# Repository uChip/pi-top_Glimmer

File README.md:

pi-top_Glimmer  
==============

NOTE: This project is a work in progress and is subject to change.  See the Status section for recent changes.  

This repository contains the design files and write-up for pi-top_Glimmer.  

Note: I have no affiliation with pi-top other than being a customer.  

The pi-top Glimmer is an accessory board for the [pi-topCEED](https://pi-top.com/product/ceed).  It also fits the pi-top laptop.  The board reconstitutes the Raspberry Pi GPIO connector. Unlike the [pi-topPROTO](https://pi-top.com/buy/addon) the Glimmer places the connector optimally for connecting the ["T-Cobbler Plus - GPIO Breakout"](https://www.adafruit.com/product/2028) or the ["Pi Wedge"](https://www.sparkfun.com/products/13717).  

<picture>

The board includes support for an IR Receiver (TSOP38238 or similar) for IR remote control of the pi-top.  An on board ATmega328p (programmable Arduino style) monitors the Raw, 5V and 3.3V voltage levels of the pi-top power supply to help detect if the supply is overloaded.  

The pi-top Glimmer passes the accessory buss through to the other end of the board so that the pi-topSPEAKER or other accessories can be plugged in.  An effort has been made to use a minimum of Raspberry Pi GPIO resources so that as many HATs as possible will still work.  The pi-top HUB board commits GPIO's 7, 9,10 & 11 as the SPI buss with HUB board select on GPIO 7 (CE1_N).  To this the pi-top Glimmer adds the use of GPIOs 2 & 3 as the I2C buss (sharable with other boards) and resides at I2C address 110.  The IR Receiver is optionally connected via solder jumper to GPIO 24 (pin 18).  

Finally, the board includes an 8x8 LED (single color, on/off) array that is refreshed from the Arduino and commanded from the pi-top's Raspberry Pi.  

The software folder contains a "sketch" that is source code for the Arduino which can be changed and updated from the pi-top.  

The board is built using a combination of through-hole and (larger scale) surface mount technologies and is reasonably easy to hand assemble. I created this board for a number of reasons; to more easily enable prototyping on the pi-top, to learn more about the pi-top's accessory buss, to experiment with I2C on both RPi and Arduino, to teach myself KiCad, and to enable future projects I have in mind.  

I did it as a one off, but it seems to have some utility for classroom scenarios.  If there is interest I would be willing to make a manufacturing run of the pi-top Glimmer as a product.  

## Order PCBs  

You can order this PCB directly from OSH Park.  Click on the following link.  
  * pi-top Glimmer - https://oshpark.com/shared_projects/x6jgBiCp  

See the Bill of Materials (BOM) file in the repo Hardware folder for a parts list.  

## Status  
  * PCB (rev 1.0beta) has been checked against components and specs and is currently out for fab.  

## File Formats  

Hardware design files are in "KiCad EDA" .kicad_pcb and .sch formats (KiCAD version: (2017-05-14 revision 14bb238b3)).  A free version of the software can be downloaded from kicad-pcb.org.  

The example code is in Arduino .ino format (text).  A free version of the Arduino software can be downloaded from www.arduino.cc.  

## Distribution License  

License:  
<br /><span xmlns:dct="http://purl.org/dc/terms/" property="dct:title">pi-top Glimmer</span> by <a xmlns:cc="http://creativecommons.org/ns#" href="https://github.com/uChip/pi-top_Glimmer" property="cc:attributionName" rel="cc:attributionURL">C.Schnarel</a> is licensed under a <a rel="license" href="http://creativecommons.org/licenses/by-sa/4.0/">Creative Commons Attribution-ShareAlike 4.0 International License</a>.

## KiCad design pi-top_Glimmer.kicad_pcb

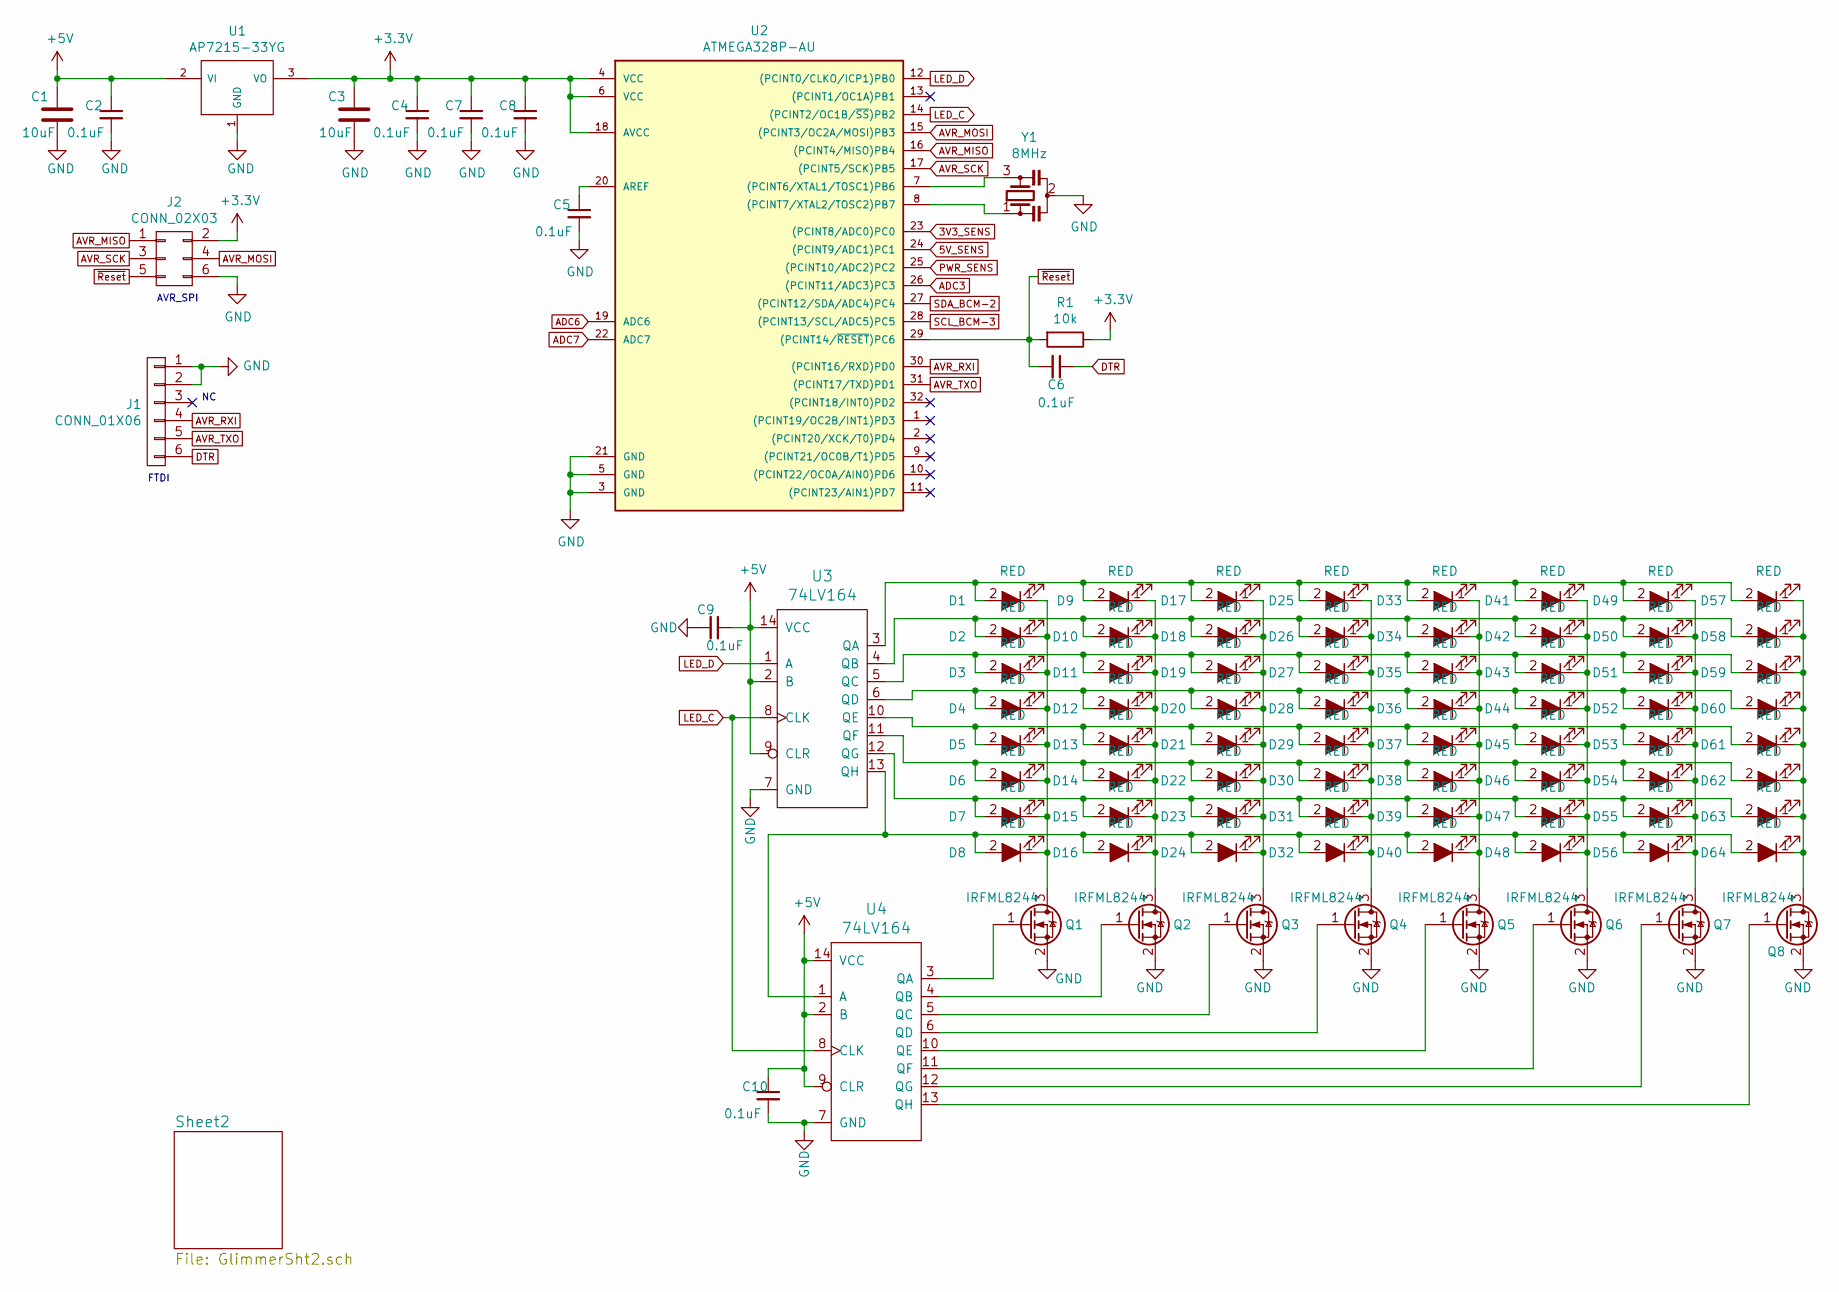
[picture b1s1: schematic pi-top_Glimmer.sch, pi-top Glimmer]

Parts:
C1, C3: 10uF; C_0805_HandSoldering
C2, C4, C5, C6, C7, C8, C9, C10: 0.1uF; C_0805_HandSoldering
D1, D2, D3, D4, D5, D6, D7, D8, D9, D10, D11, D12, D13, D14, D15, D16, D17, D18, D19, D20, D21, D22, D23, D24, D25, D26, D27, D28, D29, D30, D31, D32, D33, D34, D35, D36, D37, D38, D39, D40, D41, D42, D43, D44, D45, D46, D47, D48, D49, D50, D51, D52, D53, D54, D55, D56, D57, D58, D59, D60, D61, D62, D63, D64: RED; LED_0805
J1: CONN_01X06; Pin_Header_Straight_1x06_Pitch2.54mm
J2: CONN_02X03; Pin_Header_Straight_2x03_Pitch2.54mm
Q1, Q2, Q3, Q4, Q5, Q6, Q7, Q8: IRFML8244; SOT-23_Handsoldering
R1: 10k; R_0805_HandSoldering
U1: AP7215-33YG; SOT-89-3_Handsoldering
U2: ATMEGA328P-AU; TQFP-32_7x7mm_Pitch0.8mm
U3, U4: 74LV164; TSSOP-14_4.4x5mm_Pitch0.65mm
Y1: 8MHz; Resonator_SMD_muRata_CSTCE_3.2mm_1.3mm

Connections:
3V3_SENS: U2.23 ((PCINT8/ADC0)PC0); also elsewhere on the board
5V_SENS: U2.24 ((PCINT9/ADC1)PC1); also elsewhere on the board
+5V: C1.1, C2.1, C9.1, C10.1, U1.2 (VI), U3.2 (B), U3.9 (CLR), U3.14 (VCC), U4.2 (B), U4.9 (CLR), U4.14 (VCC); also elsewhere on the board
ADC3: U2.26 ((PCINT11/ADC3)PC3)
ADC6: U2.19 (ADC6)
ADC7: U2.22 (ADC7)
AVR_MISO: J2.1, U2.16 ((PCINT4/MISO)PB4)
AVR_MOSI: J2.4, U2.15 ((PCINT3/OC2A/MOSI)PB3)
AVR_RXI: J1.4, U2.30 ((PCINT16/RXD)PD0)
AVR_SCK: J2.3, U2.17 ((PCINT5/SCK)PB5)
AVR_TXO: J1.5, U2.31 ((PCINT17/TXD)PD1)
DTR: C6.1, J1.6
GND: C1.2, C2.2, C3.2, C4.2, C5.2, C7.2, C8.2, C9.2, C10.2, J1.1, J1.2, J2.6, Q1.2 (S), Q2.2 (S), Q3.2 (S), Q4.2 (S), Q5.2 (S), Q6.2 (S), Q7.2 (S), Q8.2 (S), U1.1 (GND), U2.3 (GND), U2.5 (GND), U2.21 (GND), U3.7 (GND), U4.7 (GND), Y1.2; also elsewhere on the board
LED_C: U2.14 ((PCINT2/OC1B/~SS~)PB2), U3.8 (CLK), U4.8 (CLK)
LED_D: U2.12 ((PCINT0/CLKO/ICP1)PB0), U3.1 (A)
unnamed: C5.1, U2.20 (AREF)
unnamed: D1.1 (K), D2.1 (K), D3.1 (K), D4.1 (K), D5.1 (K), D6.1 (K), D7.1 (K), D8.1 (K), Q1.3 (D)
unnamed: D1.2 (A), D9.2 (A), D17.2 (A), D25.2 (A), D33.2 (A), D41.2 (A), D49.2 (A), D57.2 (A), U3.3 (QA)
unnamed: D9.1 (K), D10.1 (K), D11.1 (K), D12.1 (K), D13.1 (K), D14.1 (K), D15.1 (K), D16.1 (K), Q2.3 (D)
unnamed: D2.2 (A), D10.2 (A), D18.2 (A), D26.2 (A), D34.2 (A), D42.2 (A), D50.2 (A), D58.2 (A), U3.4 (QB)
unnamed: D3.2 (A), D11.2 (A), D19.2 (A), D27.2 (A), D35.2 (A), D43.2 (A), D51.2 (A), D59.2 (A), U3.5 (QC)
unnamed: D4.2 (A), D12.2 (A), D20.2 (A), D28.2 (A), D36.2 (A), D44.2 (A), D52.2 (A), D60.2 (A), U3.6 (QD)
unnamed: D5.2 (A), D13.2 (A), D21.2 (A), D29.2 (A), D37.2 (A), D45.2 (A), D53.2 (A), D61.2 (A), U3.10 (QE)
unnamed: D6.2 (A), D14.2 (A), D22.2 (A), D30.2 (A), D38.2 (A), D46.2 (A), D54.2 (A), D62.2 (A), U3.11 (QF)
unnamed: D7.2 (A), D15.2 (A), D23.2 (A), D31.2 (A), D39.2 (A), D47.2 (A), D55.2 (A), D63.2 (A), U3.12 (QG)
unnamed: D8.2 (A), D16.2 (A), D24.2 (A), D32.2 (A), D40.2 (A), D48.2 (A), D56.2 (A), D64.2 (A), U3.13 (QH), U4.1 (A)
unnamed: D17.1 (K), D18.1 (K), D19.1 (K), D20.1 (K), D21.1 (K), D22.1 (K), D23.1 (K), D24.1 (K), Q3.3 (D)
unnamed: D25.1 (K), D26.1 (K), D27.1 (K), D28.1 (K), D29.1 (K), D30.1 (K), D31.1 (K), D32.1 (K), Q4.3 (D)
unnamed: D33.1 (K), D34.1 (K), D35.1 (K), D36.1 (K), D37.1 (K), D38.1 (K), D39.1 (K), D40.1 (K), Q5.3 (D)
unnamed: D41.1 (K), D42.1 (K), D43.1 (K), D44.1 (K), D45.1 (K), D46.1 (K), D47.1 (K), D48.1 (K), Q6.3 (D)
unnamed: D49.1 (K), D50.1 (K), D51.1 (K), D52.1 (K), D53.1 (K), D54.1 (K), D55.1 (K), D56.1 (K), Q7.3 (D)
unnamed: D57.1 (K), D58.1 (K), D59.1 (K), D60.1 (K), D61.1 (K), D62.1 (K), D63.1 (K), D64.1 (K), Q8.3 (D)
unnamed: Q1.1 (G), U4.3 (QA)
unnamed: Q2.1 (G), U4.4 (QB)
unnamed: Q3.1 (G), U4.5 (QC)
unnamed: Q4.1 (G), U4.6 (QD)
unnamed: Q5.1 (G), U4.10 (QE)
unnamed: Q6.1 (G), U4.11 (QF)
unnamed: Q7.1 (G), U4.12 (QG)
unnamed: Q8.1 (G), U4.13 (QH)
unnamed: U2.7 ((PCINT6/XTAL1/TOSC1)PB6), Y1.3
unnamed: U2.8 ((PCINT7/XTAL2/TOSC2)PB7), Y1.1
PWR_SENS: U2.25 ((PCINT10/ADC2)PC2); also elsewhere on the board
SCL_BCM-3: U2.28 ((PCINT13/SCL/ADC5)PC5); also elsewhere on the board
SDA_BCM-2: U2.27 ((PCINT12/SDA/ADC4)PC4); also elsewhere on the board
~Reset: C6.2, J2.5, R1.2, U2.29 ((PCINT14/~RESET~)PC6)

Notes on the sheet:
FTDI
AVR_SPI

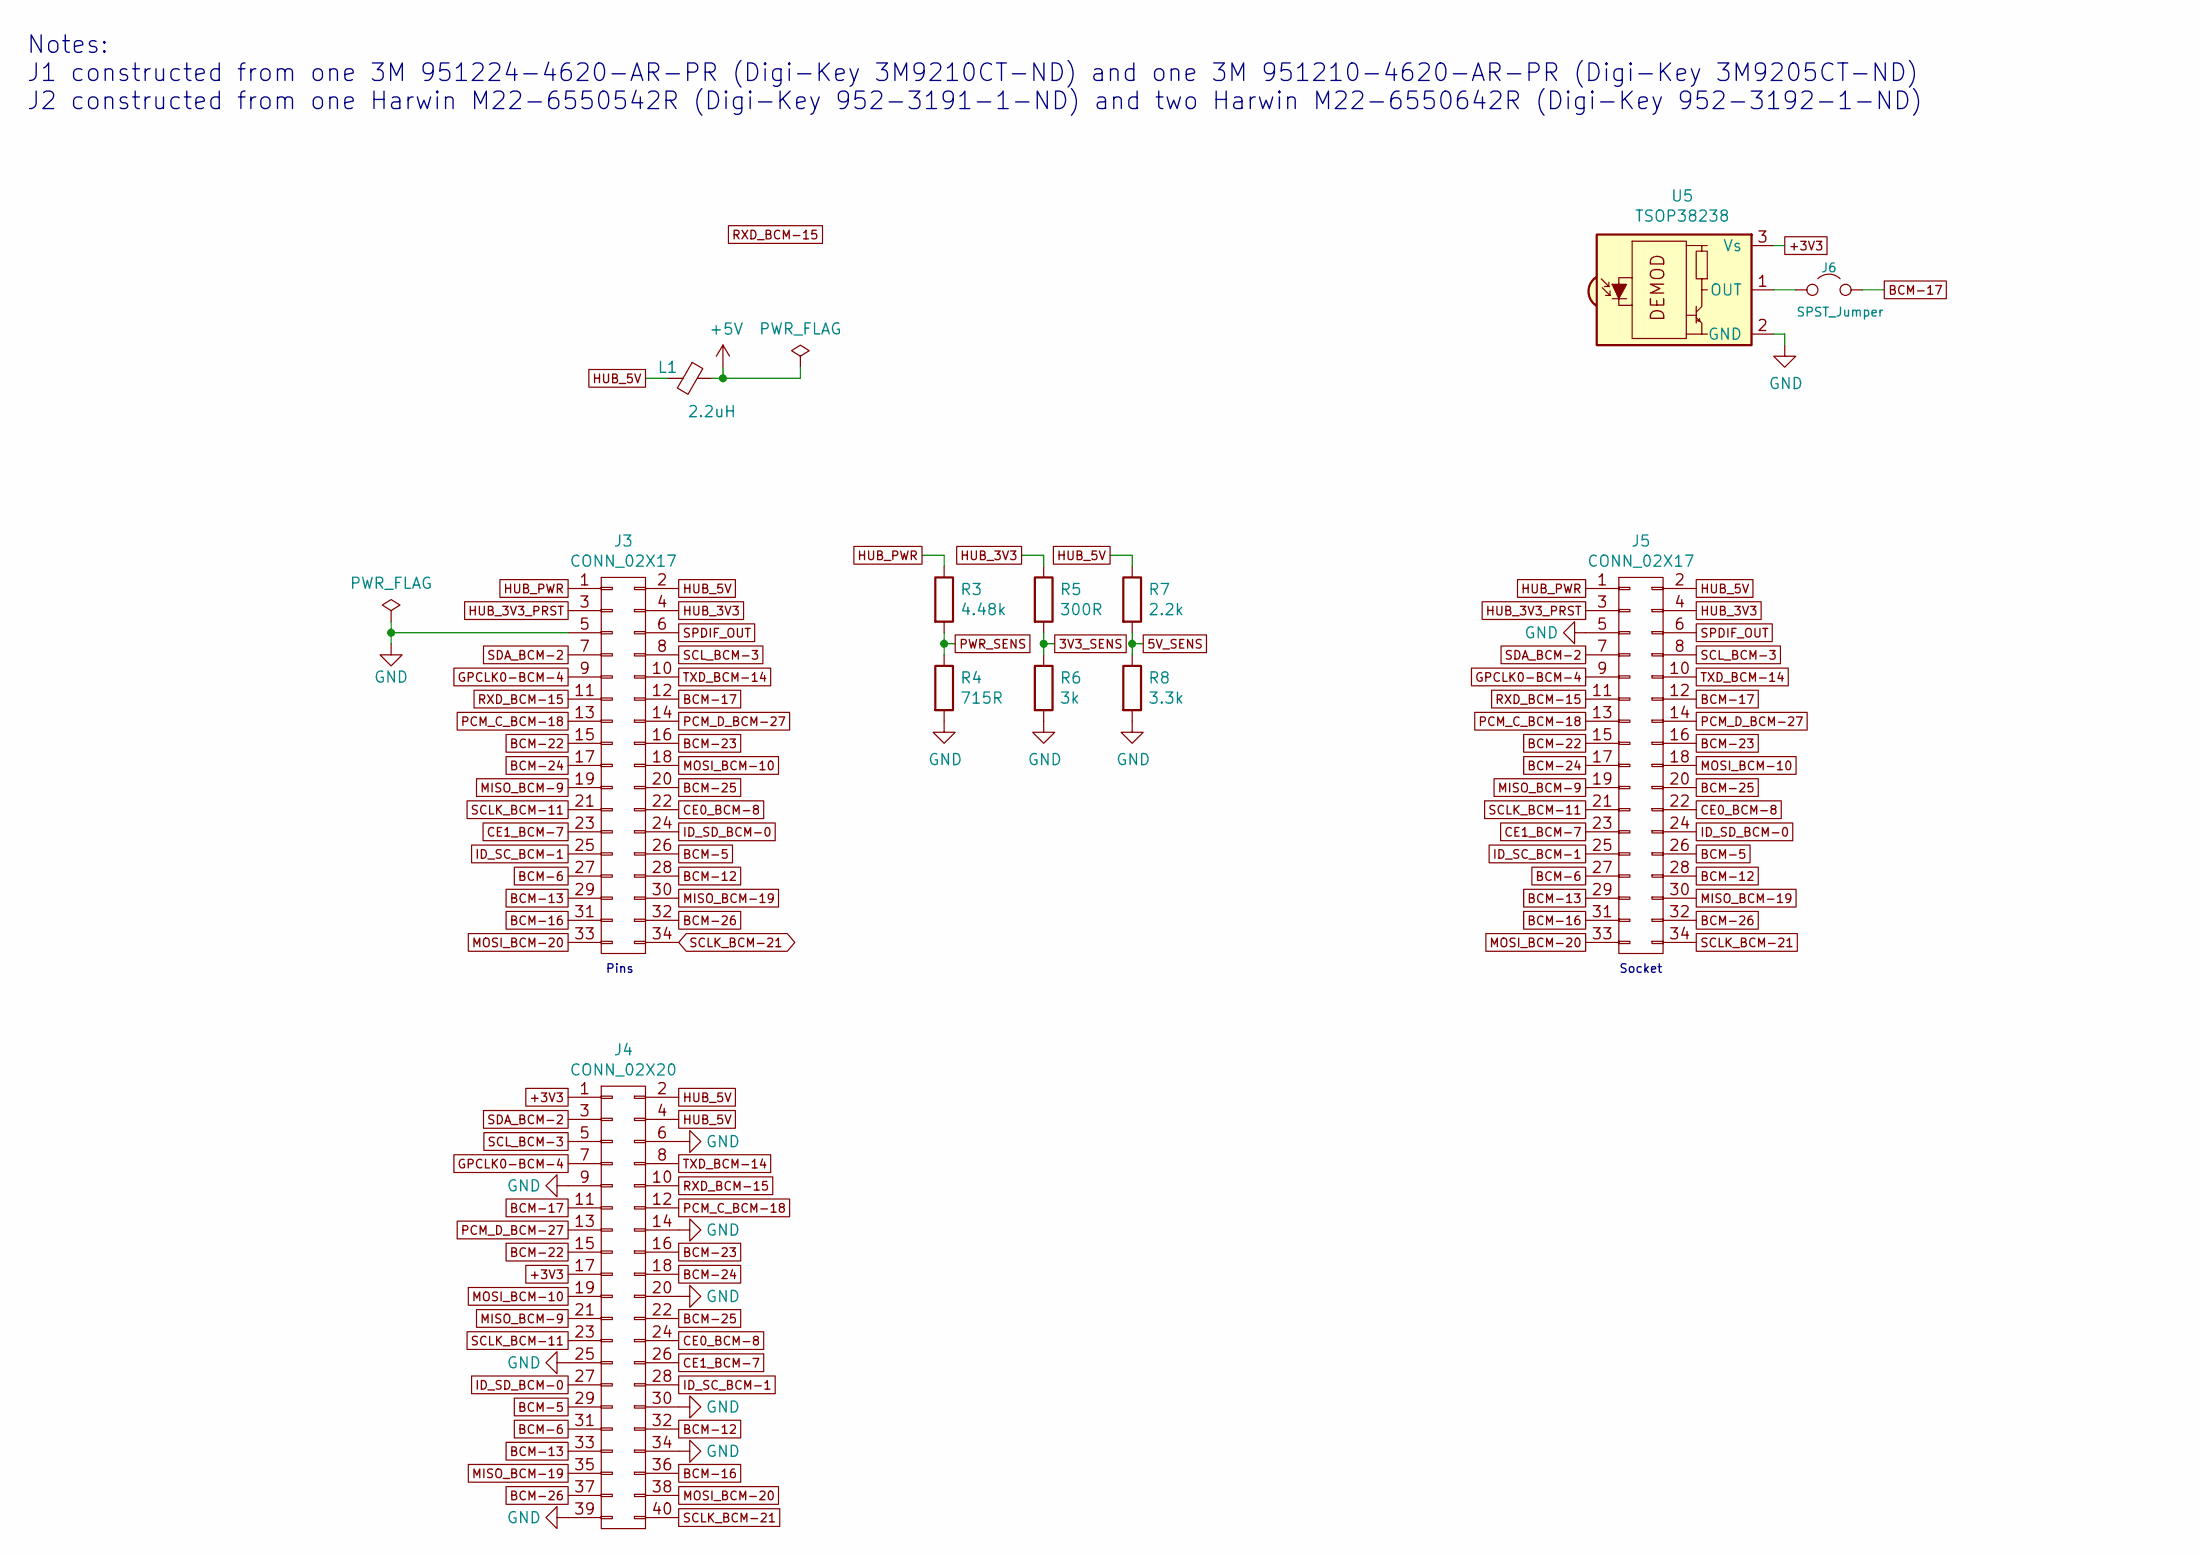
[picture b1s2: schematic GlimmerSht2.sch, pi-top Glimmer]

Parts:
J3: CONN_02X17; 3M_951217-4620-XX
J4: CONN_02X20; Pin_Header_Straight_2x20_Pitch2.54mm
J5: CONN_02X17; Harwin_M22-6553442R
J6: SPST_Jumper
L1: 2.2uH; L_0805_HandSoldering
R3: 4.48k; R_0805_HandSoldering
R4: 715R; R_0805_HandSoldering
R5: 300R; R_0805_HandSoldering
R6: 3k; R_0805_HandSoldering
R7: 2.2k; R_0805_HandSoldering
R8: 3.3k; R_0805_HandSoldering
U5: TSOP38238; IRReceiver_Vishay_MINICAST-3pin

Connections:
3V3_SENS: R5.2, R6.1; also elsewhere on the board
5V_SENS: R7.2, R8.1; also elsewhere on the board
+5V: L1.1; also elsewhere on the board
BCM-5: J3.26, J4.29, J5.26
BCM-6: J3.27, J4.31, J5.27
BCM-12: J3.28, J4.32, J5.28
BCM-13: J3.29, J4.33, J5.29
BCM-16: J3.31, J4.36, J5.31
BCM-17: J3.12, J4.11, J5.12, J6.2 (B)
BCM-22: J3.15, J4.15, J5.15
BCM-23: J3.16, J4.16, J5.16
BCM-24: J3.17, J4.18, J5.17
BCM-25: J3.20, J4.22, J5.20
BCM-26: J3.32, J4.37, J5.32
CE0_BCM-8: J3.22, J4.24, J5.22
CE1_BCM-7: J3.23, J4.26, J5.23
GND: J3.5, J4.6, J4.9, J4.14, J4.20, J4.25, J4.30, J4.34, J4.39, J5.5, R4.2, R6.2, R8.2, U5.2 (GND); also elsewhere on the board
GPCLK0-BCM-4: J3.9, J4.7, J5.9
HUB_3V3: J3.4, J5.4, R5.1
HUB_3V3_PRST: J3.3, J5.3
HUB_5V: J3.2, J4.2, J4.4, J5.2, L1.2, R7.1
HUB_PWR: J3.1, J5.1, R3.1
ID_SC_BCM-1: J3.25, J4.28, J5.25
ID_SD_BCM-0: J3.24, J4.27, J5.24
MISO_BCM-9: J3.19, J4.21, J5.19
MISO_BCM-19: J3.30, J4.35, J5.30
MOSI_BCM-10: J3.18, J4.19, J5.18
MOSI_BCM-20: J3.33, J4.38, J5.33
unnamed: J6.1 (A), U5.1 (OUT)
PCM_C_BCM-18: J3.13, J4.12, J5.13
PCM_D_BCM-27: J3.14, J4.13, J5.14
PWR_SENS: R3.2, R4.1; also elsewhere on the board
RXD_BCM-15: J3.11, J4.10, J5.11
SCLK_BCM-11: J3.21, J4.23, J5.21
SCLK_BCM-21: J3.34, J4.40, J5.34
SCL_BCM-3: J3.8, J4.5, J5.8; also elsewhere on the board
SDA_BCM-2: J3.7, J4.3, J5.7; also elsewhere on the board
SPDIF_OUT: J3.6, J5.6
TXD_BCM-14: J3.10, J4.8, J5.10

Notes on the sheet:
Pins
Socket
Notes: J1 constructed from one 3M 951224-4620-AR-PR (Digi-Key 3M9210CT-ND) and one 3M 951210-4620-AR-PR (Digi-Key 3M9205CT-ND) J2 constructed from one Harwin M22-6550542R (Digi-Key 952-3191-1-ND) and two Harwin M22-6550642R (Digi-Key 952-3192-1-ND)

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
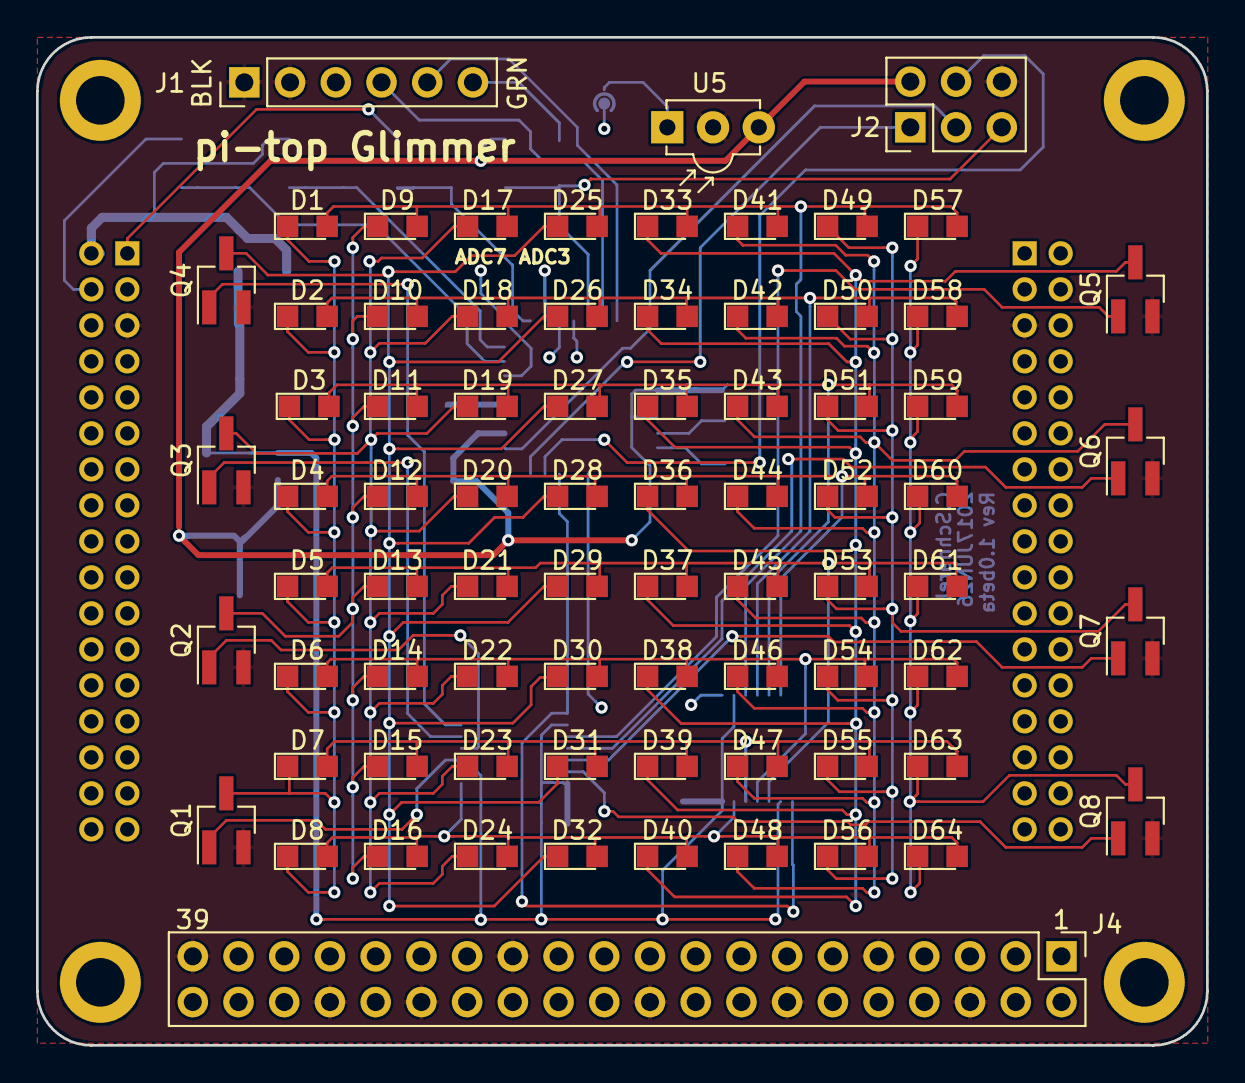
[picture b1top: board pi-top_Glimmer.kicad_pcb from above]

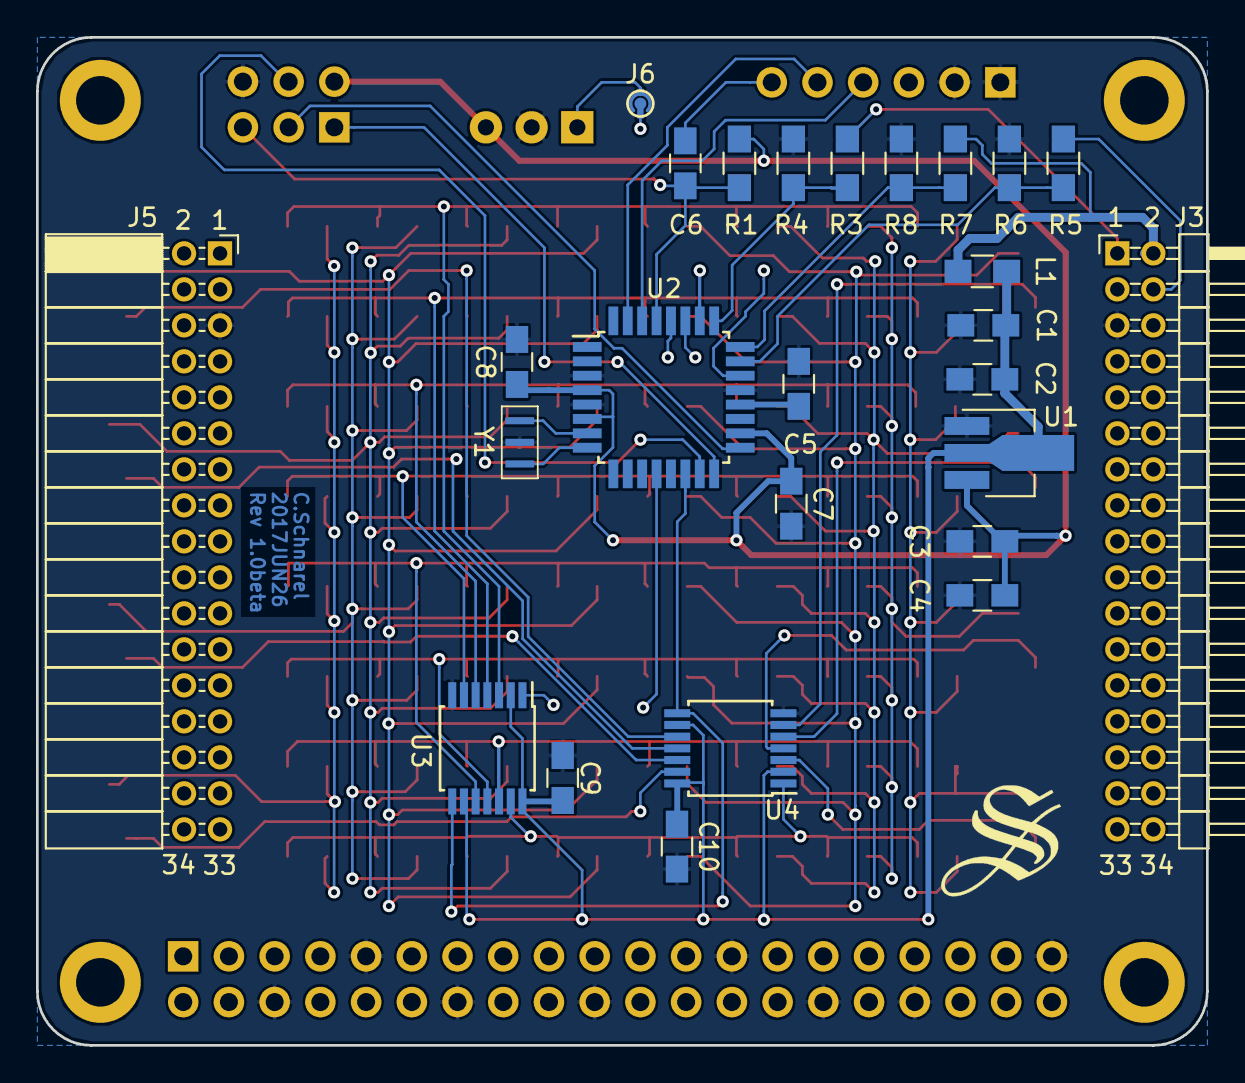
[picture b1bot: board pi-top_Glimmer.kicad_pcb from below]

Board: 4 copper layers, 65.0 x 56.0 mm, 102 parts (26 on the bottom side), 76 nets.

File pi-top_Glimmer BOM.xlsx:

pi-top_Glimmer BOM
Id | Designator | Package | Quantity | Designation | Supplier and ref | $ | $ Tot
1 | J5 | Socket_Strip_Angled_2x17_Pitch2.00mm | 1 | CONN_02X17 | Digi-Key #SAM11861-ND plus Digi-Key #SAM9981-ND | 5.79 | 5.79
2 | J3 | Pin_Header_Angled_2x17_Pitch2.00mm | 1 | CONN_02X17 | Digi-Key #3M9171-34-ND | 4.03 | 4.03
3 | J4 | Pin_Header_Straight_2x20_Pitch2.54mm | 1 | CONN_02X20 | Digi-Key #S2011EC-20-ND | 0.93 | 0.93
4 | U3,U4 | TSSOP-14_4.4x5mm_Pitch0.65mm | 2 | 74LV164 | Digi-Key #296-3788-1-ND | 0.42 | 0.84
5 | Q1,Q2,Q3,Q4,Q5,Q6,Q7,Q8 | SOT-23_Handsoldering | 8 | IRFML8244 | Digi-Key #IRFML8244TRPBFCT-ND | 0.38 | 3.04
6 | D18,D1,D2,D3,D4,D5,D6,D7,D8,D9,D10,D11,D12,D13,D14,D15,D16,D17,D19,D20,D21,D22,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 | LED_0805 | 64 | RED | Digi-Key #475-1278-1-ND or similar | 9.98E-2 | 6.3872
7 | C1,C3 | C_0805_HandSoldering | 2 | 10uF | Digi-Key #C2012X5R1V106K085AC | 0.73 | 1.46
8 | C2,C4,C5,C6,C7,C8,C9,C10 | C_0805_HandSoldering | 8 | 0.1uF | Digi-Key #CC0805ZRY5V9BB104 | 3.7999999999999999E-2 | 0.30399999999999999
9 | J1 | Pin_Header_Straight_1x06_Pitch2.54mm | 1 | CONN_01X06 | Digi-Key #609-3272-ND | 0.34 | 0.34
10 | L1 | L_0805_HandSoldering | 1 | FERRITE BEAD 2.5 KOHM 0805 1LN | Digi-Key #1276-6377-1-ND | 0.1 | 0.1
11 | R1 | R_0805_HandSoldering | 1 | 10k 1/8W 5% | Digi-Key #P10KACT-ND | 0.1 | 0.1
12 | R3 | R_0805_HandSoldering | 1 | 4.53k 1/8W 1% | Digi-Key #311-4.53KCRCT-ND | 0.1 | 0.1
13 | R4 | R_0805_HandSoldering | 1 | 715R 1/8W 1% | Digi-Key #311-715CRCT-ND | 0.1 | 0.1
14 | R5 | R_0805_HandSoldering | 1 | 300R 1/8W 1% | Digi-Key #311-300CRCT-ND | 0.1 | 0.1
15 | R6 | R_0805_HandSoldering | 1 | 3k 1/8W 1% | Digi-Key #311-3.00KCRCT-ND | 0.1 | 0.1
16 | R7 | R_0805_HandSoldering | 1 | 2.2k 1/8W 1% | Digi-Key #311-2.20KCRCT-ND | 0.1 | 0.1
17 | R8 | R_0805_HandSoldering | 1 | 3.3k 1/8W 1% | Digi-Key #311-3.30KCRCT-ND | 0.1 | 0.1
18 | U5 | IRReceiver_Vishay_MINICAST-3pin | 1 | TSOP38238 | Digi-Key #751-1227-ND | 1.1200000000000001 | 1.1200000000000001
19 | U2 | TQFP-32_7x7mm_Pitch0.8mm | 1 | ATMEGA328P-AU | Digi-Key #ATMEGA328P-AU-ND | 2.0699999999999998 | 2.0699999999999998
20 | Y1 | Resonator_SMD_muRata_CSTCE_3.2mm_1.3mm | 1 | 8MHz | Digi-Key #490-1195-1-ND | 0.48 | 0.48
21 | U1 | SOT-89-3_Handsoldering | 1 | AP7215-33YG | Digi-Key #AP7215-33YG-13DICT-ND | 0.5 | 0.5
 |  |  |  |  |  |  | 28.091200000000011

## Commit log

2017-06-22 :space_invader: Added .gitattributes & .gitignore files
2017-06-22 Creating repository
2017-06-25 Started README
2017-06-25 README
2017-06-25 README edits
2017-06-26 Added solder jumper to IR Rcvr; README edits
2017-06-27 Updated PCB renders; README edits
    Added OSH Park shared project permalink
2017-06-27 Adding BOM
    Parts availability caused change to schem2
2017-06-27 removed temp file
